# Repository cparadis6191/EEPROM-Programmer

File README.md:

EEPROM-Programmer
=================

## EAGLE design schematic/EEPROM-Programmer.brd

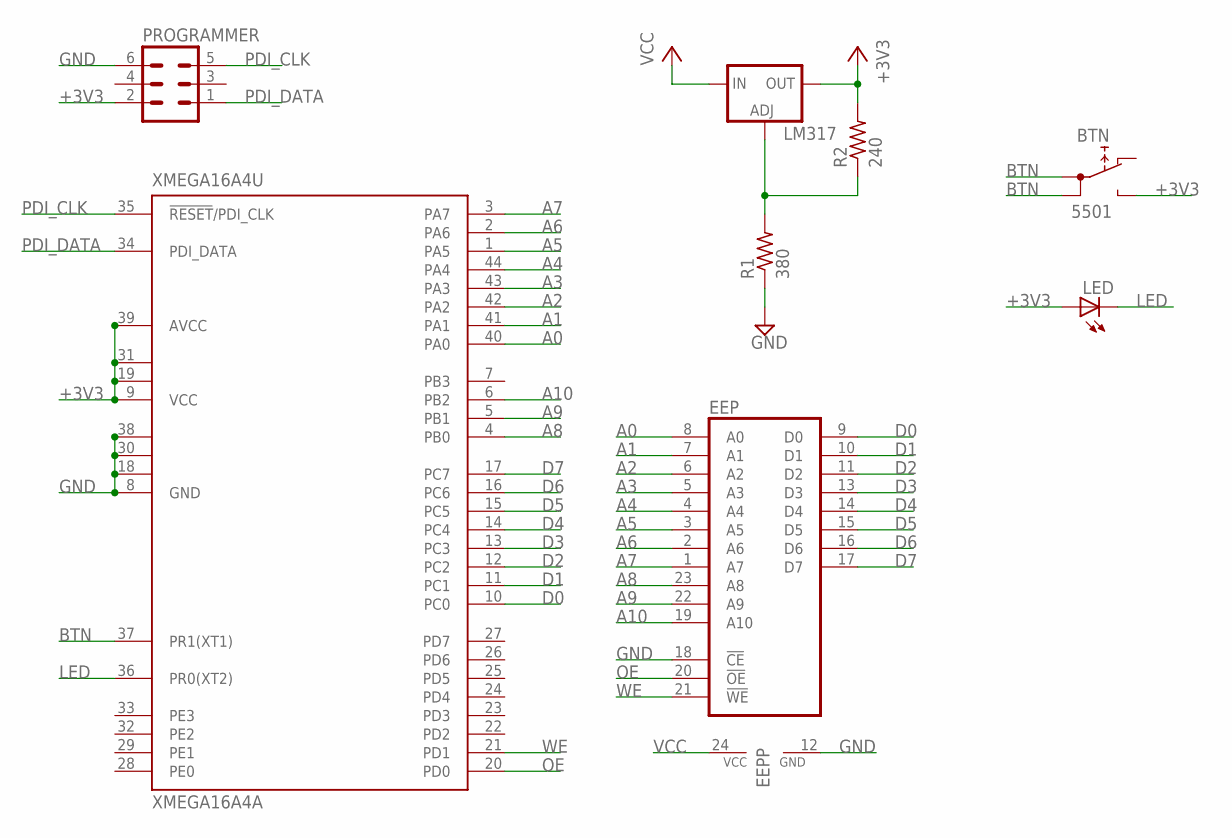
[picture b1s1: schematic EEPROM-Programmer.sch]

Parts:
BTN: 5501
EEP: 2816; DIL24
LED: LED3MM
LM317: LM317TS; 317TS
PROGRAMMER: MA03-2
R1: 380; 0204V
R2: 240; 0204V
XMEGA16A4U: XMEGA16A4A; TQFP44

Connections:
+3V3: BTN.NO, LED.A, LM317.2 (OUT), PROGRAMMER.2, R2.2, XMEGA16A4U.9 (VCC), XMEGA16A4U.19 (VCC1), XMEGA16A4U.31 (VCC2), XMEGA16A4U.39 (AVCC)
A0: EEP.8 (A0), XMEGA16A4U.40 (PA0)
A1: EEP.7 (A1), XMEGA16A4U.41 (PA1)
A2: EEP.6 (A2), XMEGA16A4U.42 (PA2)
A3: EEP.5 (A3), XMEGA16A4U.43 (PA3)
A4: EEP.4 (A4), XMEGA16A4U.44 (PA4)
A5: EEP.3 (A5), XMEGA16A4U.1 (PA5)
A6: EEP.2 (A6), XMEGA16A4U.2 (PA6)
A7: EEP.1 (A7), XMEGA16A4U.3 (PA7)
A8: EEP.23 (A8), XMEGA16A4U.4 (PB0)
A9: EEP.22 (A9), XMEGA16A4U.5 (PB1)
A10: EEP.19 (A10), XMEGA16A4U.6 (PB2)
BTN: BTN.1A, BTN.1B, XMEGA16A4U.37 (PR1(XT1))
D0: EEP.9 (D0), XMEGA16A4U.10 (PC0)
D1: EEP.10 (D1), XMEGA16A4U.11 (PC1)
D2: EEP.11 (D2), XMEGA16A4U.12 (PC2)
D3: EEP.13 (D3), XMEGA16A4U.13 (PC3)
D4: EEP.14 (D4), XMEGA16A4U.14 (PC4)
D5: EEP.15 (D5), XMEGA16A4U.15 (PC5)
D6: EEP.16 (D6), XMEGA16A4U.16 (PC6)
D7: EEP.17 (D7), XMEGA16A4U.17 (PC7)
GND: EEP.12 (GND), EEP.18 (!CE), PROGRAMMER.6, R1.1, XMEGA16A4U.8 (GND), XMEGA16A4U.18 (GND1), XMEGA16A4U.30 (GND2), XMEGA16A4U.38 (GND3)
LED: LED.K (C), XMEGA16A4U.36 (PR0(XT2))
unnamed: LM317.1 (ADJ), R1.2, R2.1
OE: EEP.20 (!OE)
PDI_CLK: PROGRAMMER.5, XMEGA16A4U.35 (!RESET!/PDI_CLK)
PDI_DATA: PROGRAMMER.1, XMEGA16A4U.34 (PDI_DATA)
VCC: EEP.24 (VCC), LM317.3 (IN)
WE: EEP.21 (!WE)

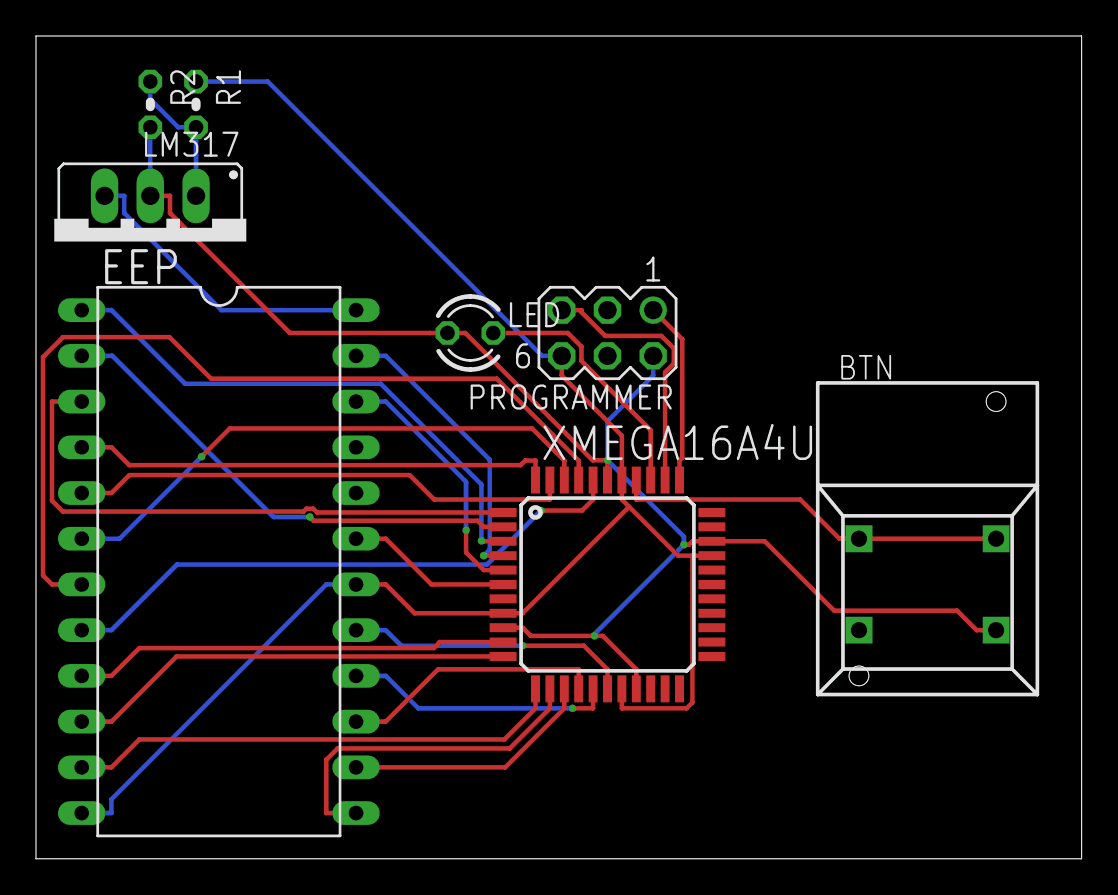
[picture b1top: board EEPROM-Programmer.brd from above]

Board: 2 copper layers, 58.1 x 45.7 mm, 8 parts (0 on the bottom side), 27 nets.

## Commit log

2013-11-29 Added main source and header files
    Added some simple init code and a main loop.
2013-11-29 Made a simple Makefile
    Makefile doesn't not dump the hex files to program the board yet.
2013-11-29 Added EEPROM source and header files
    Contains functions to initialize, write, and read. Functions are untested.
2013-12-01 Added a flag to enable c99 mode
2013-12-01 Changed EEPROM functions to read and write 4-byte words
    Three EEPROMs contain 1-byte each.
2013-12-01 Added a prototype to initialize the clock
2013-12-01 Added a simple skeleton framework for the program
    Read from UART/USB and write to EEPROM.
2013-12-01 Changed the clean target slightly
2013-12-04 Added gitignore files for both the main project and util
2013-12-04 Created a simple utility to dump board 1 binaries
    The program takes a single filename argument and outputs a file called data.h. data.h is them compiled into the project into program space memory.
2013-12-04 Added simple test code using program space hex array
2013-12-04 Added options for flashing/erasing the AVR
2013-12-04 Changed macros, fixed address length, fixed ordering
    Macros no longer have a trailing semicolon.
    Address length is now [10..0].
    Reordered some variables.
2013-12-04 Removed -r flag from the clean line
2013-12-04 Removed the root .gitignore
2013-12-04 Added schematic and board files to the repository
    Also added an Eagle gitignore file.
2013-12-08 Added Atmel Studio 6 project files
2013-12-08 Added a gitignore for the Atmel Studio stuff
2013-12-08 Added an Atmel Studio 6 project file
2013-12-08 File permissions changed a bit
2013-12-08 Migrated everything into a different directory
    Side effect of changing to an Atmel Studio 6 project.
2013-12-09 Added header and source files for I/O
    Contains macros and functions to interface with a simple LED
    and a momentary push-button.
    Both macros are written such that high is pressed/on.
2013-12-09 Changed the project to only program a single EEPROM
    The utility function will be designed to spit out three headers containing the high, middle, and low bytes of the microcode instruction.
2013-12-09 Added code to initialize I/O and wait for a button press
2013-12-09 Added a -Wextra compile switch and I/O source files
2013-12-09 Added data.h to the gitignore
    This file is generated very often and will change whenever the microcode changes.
2013-12-09 Removed data.h because it changes a lot and shouldn't be tracked
2013-12-09 Changed the circuit to only write to one EEPROM
    Removed all extra control lines and chips.
2013-12-09 Really really deleted data.h this time
2013-12-10 Modified bin2h utility to take an opcode byte argument
    Pass 1, 2, or 3 to send the low, middle, or high byte of the opcode to the header file.
    This is used for programming the low, middle, or high byte EEPROM chips.
2013-12-11 Used Freerouting to route the board
    Renamed a few lines.
2013-12-11 Added an led toggle macro and stdbool include
2013-12-11 Main loop writes full data set then waits to read back
    The button is used to read out bits.
    Reading back isn't working properly at this time.
2013-12-11 Removed some white space and changed to post increment
2013-12-11 Cleaned up some macros and added an EEPROM read function
    Read function is largely untested.
2013-12-11 Makefile and Atmel Studio 6 changes
    Makefile probably won't compile successfully.
2013-12-11 Removed the loop to read out the EEPROM
    Need some level shifters/protection for the XMEGA.
2013-12-11 Added a preprocessor warning to eeprom_read_byte
    Trying to prevent future frying of AVRs.
    Need to add some level shifters/protection for the XMEGA.
2013-12-11 Atmel Studio 6 project file changed
